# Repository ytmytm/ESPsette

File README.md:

# ESPsette

**A Wi-Fi cassette deck for your Commodore, built around an ESP-01.**
Open its page, select a TAP or PRG and type `LOAD` on the computer.
Files stream from your browser through a 12 KB buffer; you need no SD card.

Small as a *pesette* — a little scale for your LOADs.

**[Try the browser demo](https://ytmytm.github.io/ESPsette/)** without hardware.

## What works

Hardware results: **C64 PAL, 1–6 November 2026**, and **C16 PAL, 11 November 2026**.

| Feature | Status |
| --- | --- |
| TAP playback from the browser | Passed, including Rambo III Side 1 and its MOTOR pauses |
| PRG loading with standard tape pulses | Passed |
| PRG loading with the fastloader | Passed |
| Built-in Circles demo | Passed in standard and fast modes |
| WRITE filenames and command requests | Passed with an empty deck; EJECT first |
| OTA updates on a 1 MB ESP-01 | Passed over IP, including playback after updating |
| C16 PAL fastloader with 64 KB RAM | Passed on hardware, 11 November 2026; measured 7.95 kB/s |
| Other C16/Plus/4 and NTSC PRG loading and WRITE | Host/VICE tests pass; hardware tests pending |
| C16/Plus/4 TAP playback and other TAP variants | Full hardware coverage pending |
| IDX navigation and counter-based REW/FF | Host tests pass; hardware tests pending |

**C16 startup remains unreliable on the current prototype.** Successful loading
tests were performed after getting the ESP running; they do not establish
reliable startup after power-on or reset.

## Load your first program

You need an ESP-01 with at least **1 MB flash**, the Commodore interface and a
**2.4 GHz Wi-Fi network**. Your browser must be on the same local network as
the ESP. The player has no login; use it on a trusted LAN.

1. [Install the firmware using USB-UART](#install-over-usb-uart) with ESPsette
   **physically unplugged from the Commodore cassette port**.
   Disconnect the USB-UART programmer, then plug ESPsette into the cassette port.
   Turn on the C64: its cassette port powers ESPsette, which starts automatically.
   C16/Plus/4 needs a 1531 connector or adapter.
2. On first boot, join **ESPsette-XXXXXX** and choose your Wi-Fi network in the
   setup page. If it does not open automatically, visit `http://192.168.4.1/`.
   The ESP opens this setup network again if it cannot connect.
3. Rejoin your normal network. Open the ESP by its router-provided DNS name
   (for example `http://espsette.lan/`) or the IP address listed in your router.
   Its default hostname is `ESPsette`; the domain depends on your router.
4. Choose **Demo**, select a `.tap` or `.prg`, or drop a file onto the deck.
   For PRGs, first choose your computer and PAL/NTSC in **Playback settings**.
   TAP files supply their own computer profile.
5. Press **PLAY** on the page and type `LOAD` on the Commodore.
   **Autoplay** presses PLAY for you when you insert a file.
6. For a BASIC PRG loaded at standard speed, type `RUN` after loading.
   The fastloader runs it automatically. For TAPs, follow the original tape's
   loading instructions.

**Keep the browser tab open and visible until loading finishes.** The file
stays in that tab. Sleep protection helps keep the screen awake; it cannot
prevent manual locking, lid closure or OS suspension. If offered, tap
**Keep screen awake**.

### Deck controls

- **PLAY / STOP** control the virtual cassette key. The Commodore starts and
  pauses the tape through MOTOR, including the pause after the header.
- **STOP** springs back when released; the deck stays stopped. It pauses
  standard playback but cancels an active fastload.
- **REW / FF** seek with MOTOR stopped.
- **EJECT** removes the inserted file.
- For named positions, add an Ultimate-style `.idx` with your TAP, or add it
  later. Select a position and press **JUMP**, or use **PREV/NEXT**.

If the page asks you to stop MOTOR before inserting, ejecting or seeking,
cancel the current LOAD/SAVE on the Commodore. The web STOP key releases PLAY;
the computer controls MOTOR.

The elapsed time and counter refer to the whole TAP, including after a jump.
Playback settings survive a reset.

## Built-in demo

**Demo** loads [Circles](https://csdb.dk/release/?id=262238), with music by
**Shogoon** and code by **YTM**. It is for **C64 PAL only**, regardless of your
saved profile for uploaded files.

- Fastloader off: use `LOAD`, then `RUN`.
- Fastloader on: use `LOAD`; the demo loads and starts automatically.

## Use the PRG fastloader

Enable **Use fastloader for PRG** in **Playback settings**. It is off by default.
The switch saves immediately and reloads a stopped PRG in the selected mode.
Stop the transfer before changing it.

Use normal `LOAD`. A short program loads at standard speed, then receives the
rest at fast speed. The web player starts it with BASIC `RUN`; machine-code
programs need a BASIC starter for automatic launch.

TAP files keep their recorded timing. The current firmware accepts fastloader
load ranges of `$0801..$CFFF` on C64 and `$1001..$FCFF` on C16 with 64 KB RAM / Plus/4.
Use standard loading for PRGs outside those ranges.

Measured fastloader speed on real **C16 PAL hardware: 7.95 kB/s**
(user-confirmed, 11 November 2026).

During the fast stage:

- The progress bar shows bytes sent, percentage, speed and estimated time left.
- The counter shows the equivalent standard tape time, so it advances rapidly.
- The reels spin faster and pause while waiting for data or the computer.
- Progress stays at 100% until you rewind or eject.

If a PRG fails to load, try standard loading. You can also expand
**Advanced fastloader timings** and increase the delays:

- **Save fastloader settings** saves the numeric timings for the next load.
- **Default timings** restores the fields; press Save to apply them.

The fastloader switch and timings remain saved after a reset.
[Protocol and timing details](experiments/fastloader/README.md) are available
for troubleshooting.

## Read the display

- **Wi-Fi icon:** signal between the ESP and router. Hover for RSSI in dBm.
- **BUF:** how much of the ESP's streaming buffer is filled.
- **Playback details:** loading phase, errors and screen sleep protection.
- **Debug / ESP state:** current firmware ID, reset reason, memory and buffer
  diagnostics. If loading stops unexpectedly, copy this JSON before resetting
  or ejecting.

During PLAY, the display receives compact status updates. Full diagnostics and
the waveform refresh after STOP, completion or an error.

If a load fails, save the Debug JSON first. Then stop MOTOR on the Commodore
and press **REW** to restart from the file retained in the tab. If the tab has
been closed or reloaded, select the file again.

## Receive WRITE requests

The ESP can display names sent by the Commodore's SAVE command.
It does not record the program to a file.

1. **EJECT** any TAP or PRG, even if loading has already finished.
2. Press **PLAY** on the page.
3. On the Commodore, enter `SAVE "NAZWA",1`.
4. Look for the verified filename in **Playback details**.

Names beginning with `ESP:`, such as `SAVE "ESP:TEST",1`, publish a command
request. **There are no command handlers or planned uses yet; requests do not
execute anything.** The deck must stay empty while receiving WRITE.

See the [WRITE guide](docs/WRITE-COMMANDS.md) for the request format and details.

## Install over USB-UART

Download the 1 MB firmware package from
[Releases](https://github.com/ytmytm/ESPsette/releases), or
[build it from source](#build-from-source). The package includes `FLASHING.txt`
and SHA-256 checksums.

Use the **uncompressed `.bin`** for serial flashing. The image includes Circles;
no separate filesystem image is needed.

### Connect the programmer

**Physically unplug ESPsette from the Commodore cassette port before connecting
USB-UART, even if the computer is switched off.** Keep it unplugged throughout
USB-UART flashing. Disconnect USB-UART completely before reconnecting ESPsette to
the cassette port.

Use **3.3 V power and UART logic**, with a supply able to handle Wi-Fi current
peaks. If your CH340G adapter has a voltage switch, select **3.3 V** and verify
its signal levels.

Keep **GPIO0 connected to GND throughout flashing**:

| USB-UART / supply | ESP-01 |
| --- | --- |
| 3.3 V | VCC and CH_PD / EN |
| GND | GND and GPIO0 (flash jumper) |
| TXD | RXD / GPIO3 |
| RXD | TXD / GPIO1 |
| DTR | RST |
| No connection | GPIO2 (must stay HIGH at reset), CTS, RTS |

The PCB routes the TX/RX crossover. Its programmer header is
`GND / CTS / VCC / TXD / RXD / DTR`; CTS is unused.
Our [esptool configuration](esptool.cfg) pulses DTR only. Without DTR, briefly
pull RST to GND while GPIO0 is grounded before flashing.

If the adapter is missing from your serial ports, check its
[CH340 driver](https://github.com/hobbycomponents/ch340-drivers).

### Flash and restart

For a downloaded binary, follow its `FLASHING.txt` to write it at `0x0`.
From a [prepared source checkout](#build-from-source), use:

```sh
make flash-id PORT=/dev/ttyUSB0          # Check the module's flash size
make flash PROFILE=1m PORT=/dev/ttyUSB0  # Build and upload
```

On macOS, use your `/dev/cu.usbserial-...` port; `ls /dev/cu.*` lists ports.
`make chip-info PORT=...` prints additional chip information.

After flashing:

1. Disconnect the USB-UART programmer completely and remove the GPIO0–GND jumper.
2. Connect ESPsette to the cassette port according to the [wiring notes](kicad/WIRING.md).
3. Turn on the C64; ESPsette starts from cassette-port power.

## Update over Wi-Fi

OTA is enabled for 1 MB and 4 MB modules. If your installed firmware has OTA
disabled, install this version over USB-UART first.

**For OTA, leave ESPsette connected to the powered-on C64/C16.** The computer
supplies its power. The disconnection requirement above applies to USB-UART
flashing; stop MOTOR and transfers for OTA.

From a [prepared source checkout](#build-from-source):

1. Stop MOTOR and all transfers.
2. Build and upload the checkout's firmware over your local network:

   ```sh
   make ota PROFILE=1m OTA_HOST=DEVICE_IP
   ```

3. After the ESP restarts, **refresh its page**.
4. Check **Network / OTA → Firmware** against the expected commit ID.

`OTA_HOST` accepts an IP address or a name resolved by your router, such as
`espsette.lan`. mDNS discovery is disabled; your router's local DNS still works.
OTA preserves settings and Wi-Fi configuration. It has no password by default;
you can [configure one](include/local_ota.h.example).

OTA uses `.bin.gz`, which the bootloader decompresses. Each build checks that
the update fits in flash alongside the running image and saved settings.

### Change the Wi-Fi network

To change the saved Wi-Fi network, stop MOTOR and use
**Network / OTA → Forget Wi-Fi…**. This opens a confirmation page; confirming
restarts the ESP into Wi-Fi setup. OTA updates keep the saved network.

### Check the firmware version

The page shows the running ESP's 12-character Git commit ID. Release filenames
contain the same ID, for example:

```text
ESPsette-esp01-1m-v2026-11-01-0123456789ab.bin.gz
```

`make build`, `make flash` and `make ota` print the ID. `make version` shows it
without building. A `-dirty` suffix means the checkout had local changes at
build time. The commit hash identifies the revision; use release notes and
dates to choose an update.

## Build from source

You need `make`, `curl`, Python 3, **ACME** (6502 assembler) and internet access
for the first tool download.

- Debian/Ubuntu: install ACME with `sudo apt-get install acme`.
- macOS: use `brew install acme`; install Command Line Tools with
  `xcode-select --install` if needed.

Run from the repository root:

```sh
make setup             # Download the build tools
make build PROFILE=1m  # Assemble the loaders and compile the firmware
```

`make setup` installs tools under `tools/bin/` and `~/.cache/ESPsette/`.
No global PlatformIO installation is needed. `make build` assembles the native
fastloader automatically; `make native` builds just the 6502 code.

| Profile | Module |
| --- | --- |
| `1m` (default) | 1 MB flash; OTA enabled |
| `4m` | 4 MB flash; OTA enabled |
| `512k` | Experimental; the default OTA image does not fit |

Release packages target 1 MB modules. The `512k` profile inherits OTA settings;
a build without OTA needs separate size and hardware checks.

## Hardware files

This branch uses **SENSE on GPIO0, MOTOR on GPIO1, WRITE on GPIO2 and READ
on GPIO3**. The updated schematic and PCB include isolation jumpers
JP1–JP4 for those four signals, a 1 kΩ series resistor in MOTOR, and 10 kΩ
pull-ups on GPIO0, GPIO2 and RESET. JP5 connects EN to 3.3 V and must remain
closed for normal operation. These changes support prototype testing;
the C16 startup issue above remains unresolved.

- [Wiring and ESP-01 connections](kicad/WIRING.md)
- [Schematic PDF](kicad/plots/espsette.pdf)
- [Gerber and drill files](kicad/gerbers/)
- [KiCad project](kicad/espsette.kicad_pro) and [connection plan](kicad/PLAN_POLACZEN.md)
- [Symbols, footprints and 3D models](kicad/libraries/README.md)

<details>
<summary>Local preview, tests and releases</summary>

Use `make preview` or open [web/player.html](web/player.html) to try the UI
locally. The [hosted demo](https://ytmytm.github.io/ESPsette/) also runs without
hardware. Both simulate loading and WRITE reception; preview settings stay in
browser local storage. Fonts, graphics and screen-wake media work offline.

Host tests need Node.js and a C++17 compiler. See [test instructions](tests/README.md),
[native fastloader sources](native/fastloader/) and
[fastloader protocol](experiments/fastloader/README.md).
For navigation tests, use [ui-test.tap](tests/fixtures/ui-test.tap) with
[ui-test.idx](tests/fixtures/ui-test.idx).

GitHub Actions builds the 1 MB firmware and runs host tests on pushes, pull
requests and manual runs. Its artifact includes `.bin`, `.bin.gz`, the debug
ELF, build metadata, checksums and `FLASHING.txt`. The package JSON, instructions
and Actions summary record the full commit ID.

### Release checklist

- [ ] Choose the commit and confirm its Actions tests and build pass.
- [ ] Download the artifact, verify `SHA256SUMS.txt` and flash the packaged `.bin`.
- [ ] Check cold boot, Wi-Fi setup/fallback and the player on desktop and phone.
- [ ] On C64 PAL, load a TAP and standard/fast PRGs, including Circles; check MOTOR pauses.
- [ ] EJECT, press PLAY and check WRITE reception; inserting a file must block it.
- [ ] Test OTA and compare **Network / OTA → Firmware** with the package filename.
- [ ] Update the tested features and limitations above with hardware results.
- [ ] Check the wiring and flashing instructions against the tested setup.
- [ ] Publish a GitHub Release tagged `vYYYY-MM-DD` with a valid calendar date.
- [ ] Confirm the workflow attached the firmware, metadata, instructions and checksums.

Publishing the release builds and attaches its package. Pushing a tag alone
does not publish a release.

</details>

## References

- [Ultimate Tape Archive](https://uta.pokefinder.org/)
- [VICE TAP format](https://vice-emu.sourceforge.io/vice_17.html) and [counter model](https://github.com/VICE-Team/svn-mirror/blob/main/vice/src/datasette/datasette.c)
- [Tapuino](https://github.com/sweetlilmre/tapuino) and [TapuinoNext](https://github.com/sweetlilmre/TapuinoNext)
- [TAP/IDX notes](https://www.luigidifraia.com/technical-info/#TAP_Index_format_IDX) and [Ultimate index implementation](https://github.com/GideonZ/1541ultimate/blob/master/software/filetypes/filetype_tap.cc)
- [ESP8266 boot modes](https://docs.espressif.com/projects/esptool/en/latest/esp8266/advanced-topics/boot-mode-selection.html), [PlatformIO](https://docs.platformio.org/en/latest/platforms/espressif8266.html) and [Arduino OTA](https://arduino-esp8266.readthedocs.io/en/latest/ota_updates/readme.html)

No license has been selected yet.

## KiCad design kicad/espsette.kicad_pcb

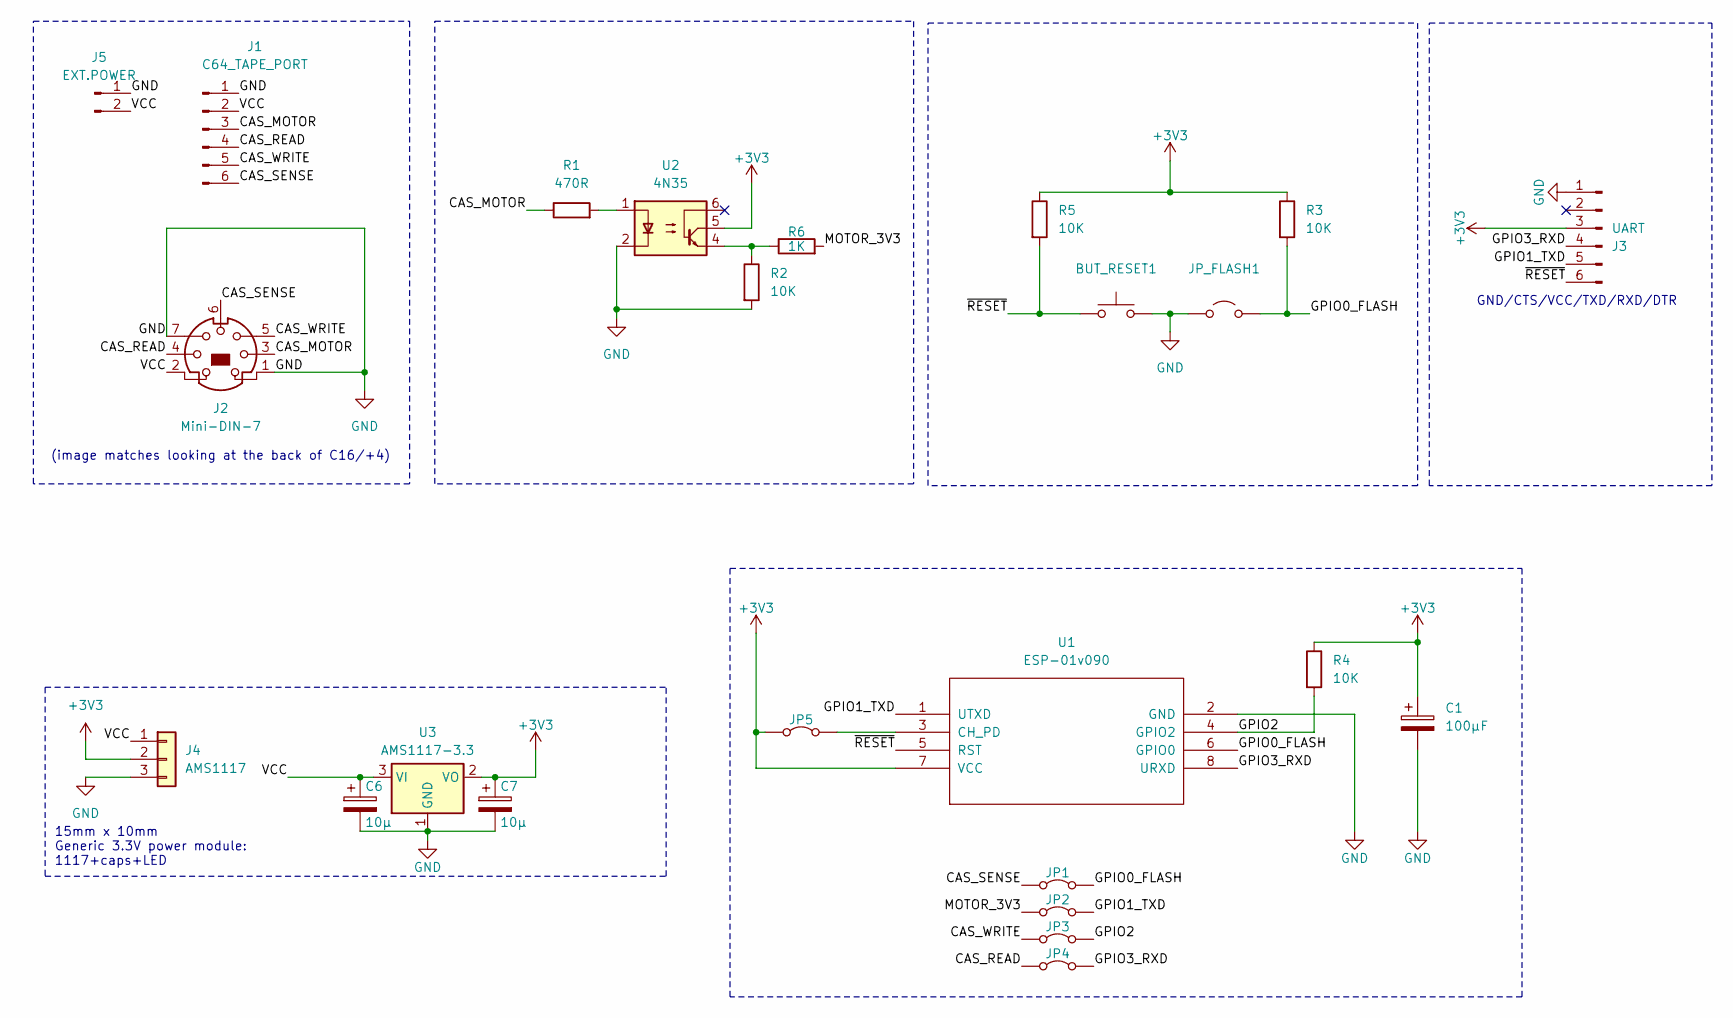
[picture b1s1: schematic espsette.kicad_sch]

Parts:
BUT_RESET1: BUT_RESET; SW_PUSH_6mm
C1: 100µF; CP_Radial_D8.0mm_P3.50mm
C6, C7: 10µ; CP_EIA-3216-12_Kemet-S_HandSolder; JLCPCB Part # C1969735
J1: C64_TAPE_PORT; C64-Cassette-Port-Female
J2: Mini-DIN-7; Mini_DIN_round_7_canned
J3: UART; PinHeader_1x06_P2.54mm_Vertical
J4: AMS1117; PinHeader_1x03_P2.54mm_Vertical
J5: EXT.POWER; PinHeader_1x02_P2.54mm_Vertical
JP1, JP2, JP3, JP4, JP5: Jumper_2_Bridged; SolderJumper-2_P1.3mm_Bridged_RoundedPad1.0x1.5mm
JP_FLASH1: JP_FLASH; PinHeader_1x02_P2.54mm_Vertical
R1: 470R; R_Axial_DIN0207_L6.3mm_D2.5mm_P7.62mm_Horizontal
R2, R3, R4, R5: 10K; R_Axial_DIN0207_L6.3mm_D2.5mm_P7.62mm_Horizontal
R6: 1K; R_Axial_DIN0207_L6.3mm_D2.5mm_P7.62mm_Horizontal
U1: ESP-01v090; ESP-01
U2: 4N35; DIP-6_W7.62mm
U3: AMS1117-3.3; SOT-223-3_TabPin2; JLCPCB Part # C6186

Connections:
+3V3: C1.1, C7.1, J3.3, J4.2, JP5.2 (B), R3.1, R4.1, R5.1, U1.7 (VCC), U2.5, U3.2 (VO)
/CAS_MOTOR: J1.3, J2.3, R1.1
/CAS_READ: J1.4, J2.4, JP4.2 (B)
/CAS_SENSE: J1.6, J2.6, JP1.2 (B)
/CAS_WRITE: J1.5, J2.5, JP3.2 (B)
/GPIO0_FLASH: JP1.1 (A), JP_FLASH1.2 (B), R3.2, U1.6 (GPIO0)
/GPIO1_TXD: J3.5, JP2.1 (A), U1.1 (UTXD)
/GPIO2: JP3.1 (A), R4.2, U1.4 (GPIO2)
/GPIO3_RXD: J3.4, JP4.1 (A), U1.8 (URXD)
/MOTOR_3V3: JP2.2 (B), R6.2
/VCC: C6.1, J1.2, J2.2, J4.1, J5.2, U3.3 (VI)
/~RESET: BUT_RESET1.1, J3.6, R5.2, U1.5 (RST)
GND: BUT_RESET1.2, C1.2, C6.2, C7.2, J1.1, J2.1, J2.7, J3.1, J4.3, J5.1, JP_FLASH1.1 (A), R2.2, U1.2 (GND), U2.2, U3.1 (GND)
unnamed: JP5.1 (A), U1.3 (CH_PD)
unnamed: R1.2, U2.1
unnamed: R2.1, R6.1, U2.4

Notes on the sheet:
GND/CTS/VCC/TXD/RXD/DTR
(image matches looking at the back of C16/+4)
15mm x 10mm Generic 3.3V power module: 1117+caps+LED

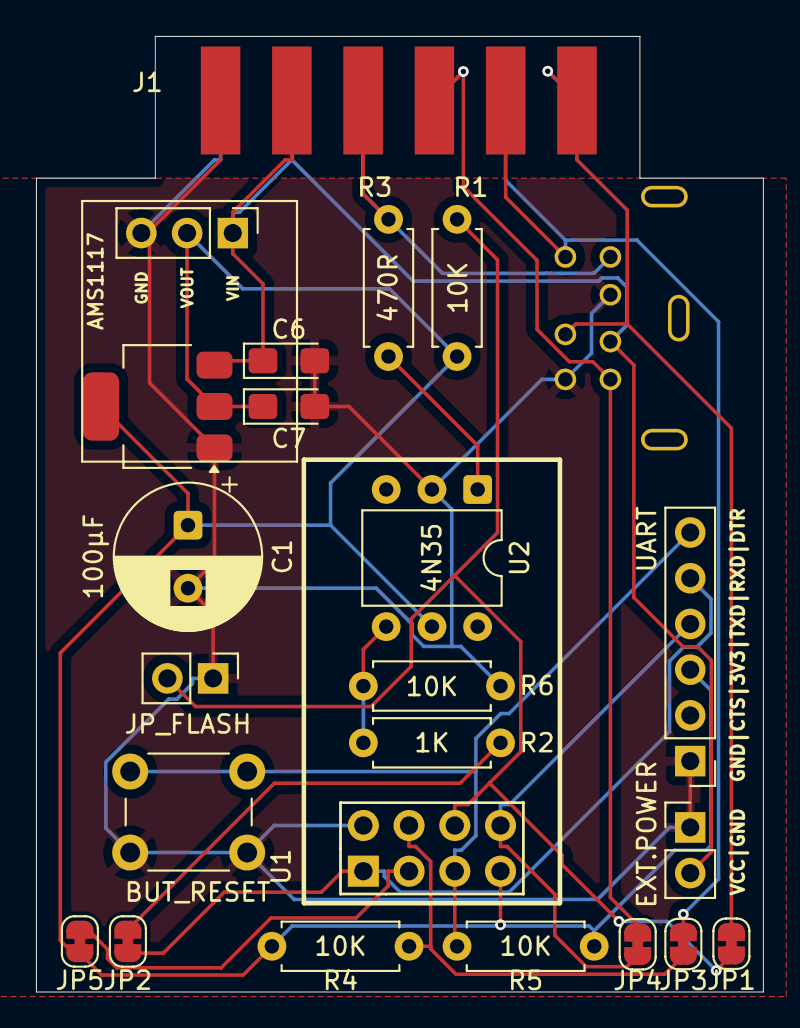
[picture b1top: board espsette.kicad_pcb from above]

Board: 2 copper layers, 40.4 x 53.1 mm, 24 parts (0 on the bottom side), 16 nets.

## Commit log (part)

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2021-05-03 simple state machine
2021-05-03 first tries at i2s streaming
2021-05-03 taptask example, also too fast
